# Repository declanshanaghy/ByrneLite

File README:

Simple 3 port S108T02 Solid State Relay controller board 

Features
========
* Handles up to 125VAC / 8A (Heatsinks needed > 2A)
* Onboard AT-Tiny85 microcontroller
* No onboard voltage regulation for logic 
  (requires externally regulated 5V power supply) 
* SSR LED on/off indicators
* On/Off switch
* On/Off indicator LED

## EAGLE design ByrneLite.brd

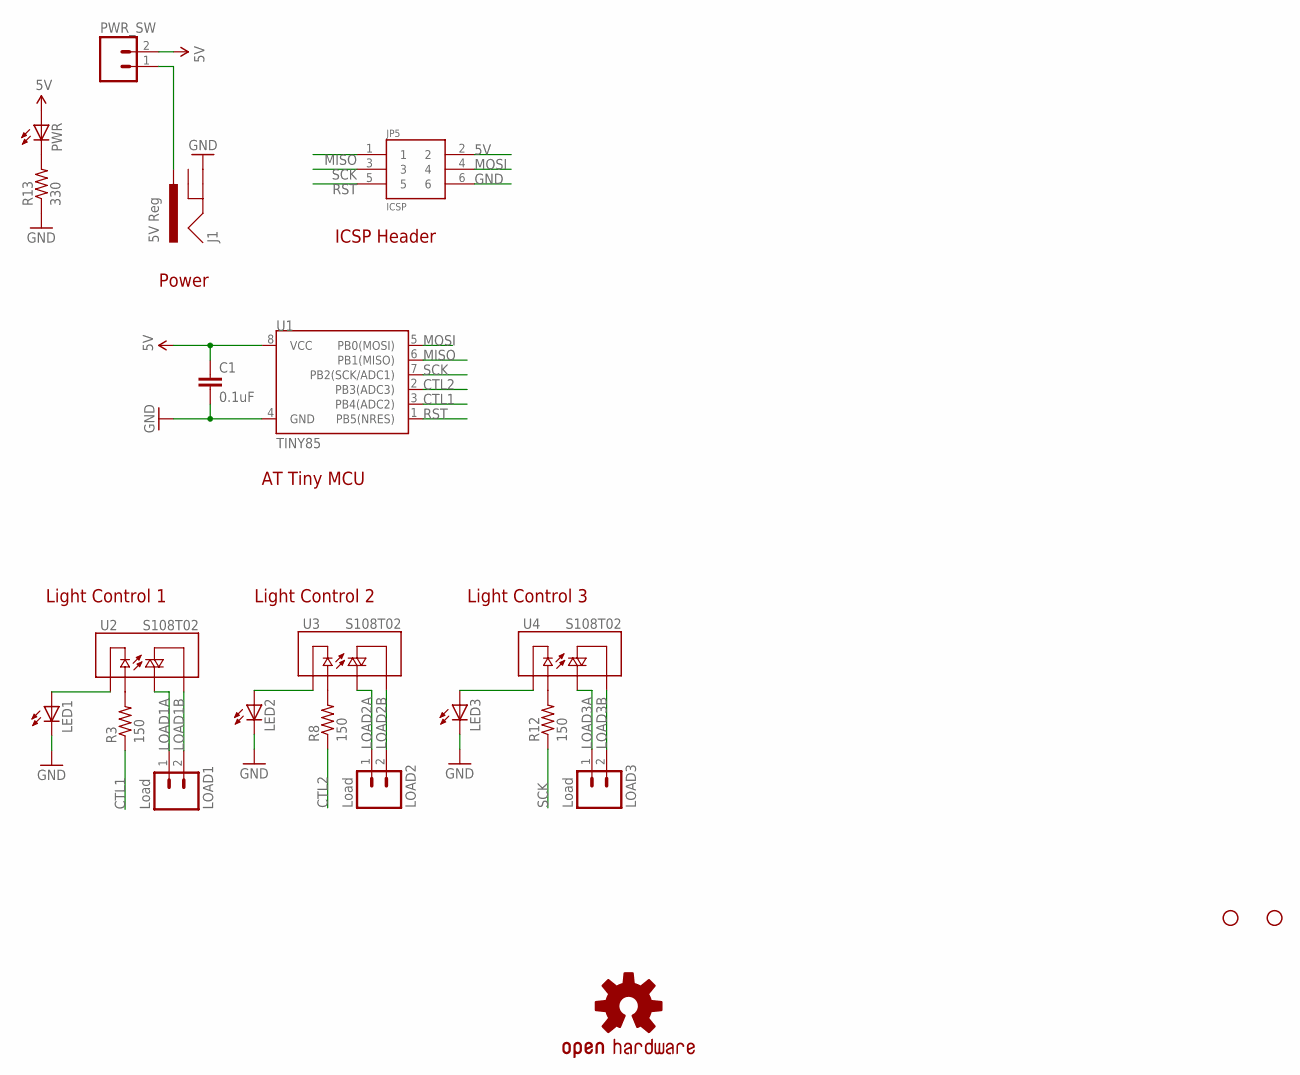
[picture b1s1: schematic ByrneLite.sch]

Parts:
C1: 0.1uF; CAP-PTH-SMALL2
J1: 5V Reg; POWER_JACK_PTH_LOCK
JP5: ICSP; 2X3-SHROUDED
LED1, LED2, LED3: LED5MM
LOAD1, LOAD2, LOAD3: Load; SCREWTERMINAL-5MM-2
LOGO1: OSHW-LOGOM; OSHW-LOGO-M
PWR: LED3MM
PWR_SW: M02PTH3; 1X02_LONGPADS
R3, R8, R12: 150; AXIAL-0.3
R13: 330; AXIAL-0.3
STANDOFF2, STANDOFF4: STAND-OFF
U1: TINY85; DIP08
U2, U3, U4: S108T02; RELAY-S108T02

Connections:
5V: C1.1, JP5.2, PWR.A, PWR_SW.2, U1.8 (VCC)
CTL1: R3.P$1 (1), U1.3 (PB4(ADC2))
CTL2: R8.P$1 (1), U1.2 (PB3(ADC3))
GND: C1.2, J1.GND, JP5.6, LED1.K (C), LED2.K (C), LED3.K (C), R13.P$1 (1), U1.4 (GND)
LOAD1A: LOAD1.1, U2.2 (T2)
LOAD1B: LOAD1.2, U2.1 (T1)
LOAD2A: LOAD2.1, U3.2 (T2)
LOAD2B: LOAD2.2, U3.1 (T1)
LOAD3A: LOAD3.1, U4.2 (T2)
LOAD3B: LOAD3.2, U4.1 (T1)
MISO: JP5.1, U1.6 (PB1(MISO))
MOSI: JP5.4, U1.5 (PB0(MOSI))
unnamed: R3.P$2 (2), U2.3 (+)
unnamed: LED2.A, U3.4 (-)
unnamed: R8.P$2 (2), U3.3 (+)
unnamed: LED3.A, U4.4 (-)
unnamed: J1.PWR, PWR_SW.1
unnamed: LED1.A, U2.4 (-)
unnamed: R12.P$2 (2), U4.3 (+)
unnamed: PWR.K (C), R13.P$2 (2)
RST: JP5.5, U1.1 (PB5(NRES))
SCK: JP5.3, R12.P$1 (1), U1.7 (PB2(SCK/ADC1))

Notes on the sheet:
Light Control 1
Light Control 3
Light Control 2
ICSP Header
AT Tiny MCU
Power

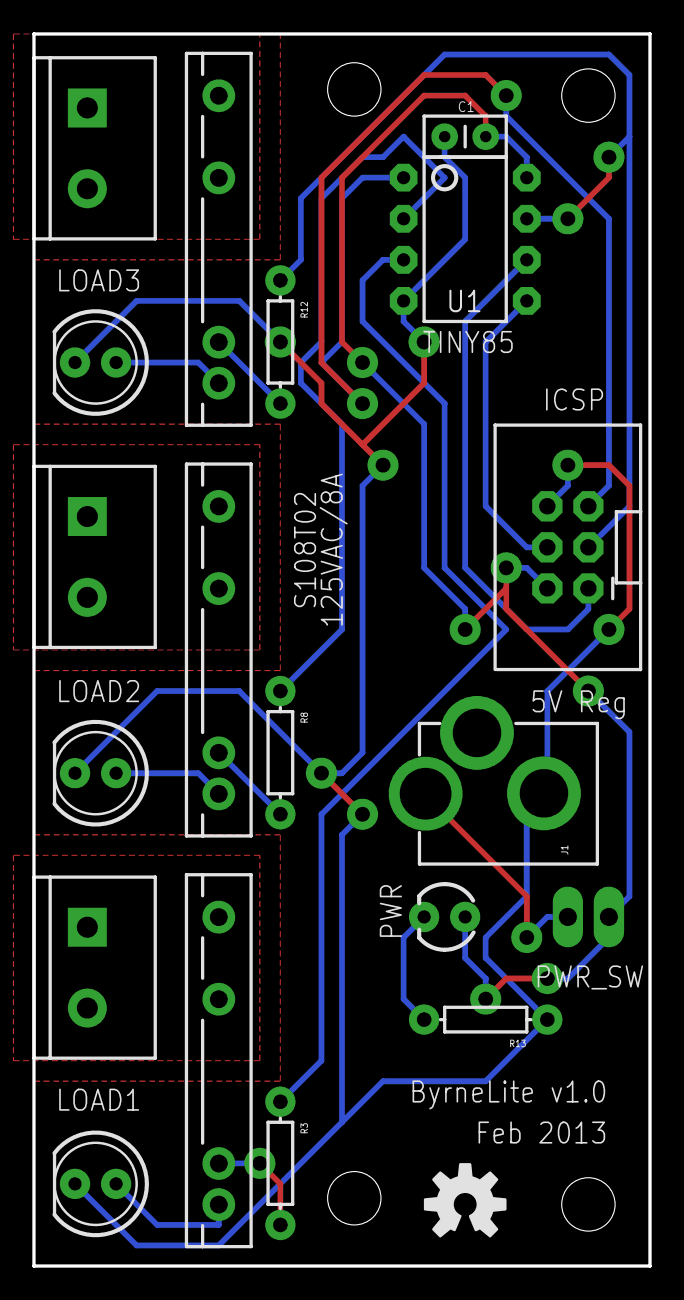
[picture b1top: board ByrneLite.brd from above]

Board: 2 copper layers, 38.1 x 76.2 mm, 24 parts (0 on the bottom side), 22 nets.

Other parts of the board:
STANDOFF1, STANDOFF3: STAND-OFF

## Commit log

2013-02-15 Generated gerbers for v1
2013-02-22 Changed to LGPL license

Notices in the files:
parts and their libraries:
SparkFun-DigitalIC: Licensing: CC v3.0 Share-Alike You are welcome to use this library for commercial purposes.
